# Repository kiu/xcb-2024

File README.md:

# xcb-2024
The cross communication badge (xcb) was created for a two day internal company conference. Its main purpose was to gamify communication and networking across the 150 participants.

<sup>Additional images can be found in the [img](img/) directory</sup>

# Features
The badge features three modes: Conference, Play and Sensor.

In <ins>conference mode</ins> each badge transmits its unique ID every 30 seconds. Any badge receiving two transmissions from the same badge within 100 seconds will count this as a unique contact. Due to limited infrared power, close proximity between sender and receiver is assumed. The amount of unique contacts is displayed on the LCD screen to gamify in-person encounters.

In addition secret badges are hidden at the event location, offering a treasure hunt for those who want to explore beyond the main conference tracks. The needed hints are printed on [flyers](xcb-2024-flyer.pdf) handed out with the badge. The discovery of these secret badges is encoded in the display as single segments to easily compare progress between participants.

It was important to me that the badge could be re-used after the conference so I added two additional modes.

In <ins>play mode</ins> the badge features a version of the popular game Simon https://en.wikipedia.org/wiki/Simon_(game) (in Germany known as Senso https://de.wikipedia.org/wiki/Senso_(Spiel)). People can chase a high score, which can also be displayed when in conference mode.

In <ins>sensor mode</ins> the badge transforms into a temperature and humidity display with min/max functionality. Powered by USB the badge can continue to operate in the home or office.

On the back of this stacked PCB assembly (preventing any electrical shorts while wearing) the participants can find a [silk screened word puzzle](img/xcb-2024-bottom-revb-render-back.png) containing the names of the employees of the company.

## Video
There is a short video highlighting all badge features on youtube: https://youtu.be/XA52-lHTVL4

# Hardware
The hardware is [straight forward](kicad/xcb-2024-top-revb-schematic.png). Powered by two CR2032 coin cells or USB, a STM32, a three digit LCD display, an infrared receiver/transmitter, a buzzer, four capacitive touch buttons and a temperature and humidity sensor. All neatly packed into a wearable badge.

# Repository
- [datasheets](datasheets/): Datasheets of most components
- [firmware](firmware/): STM32CubeIDE project
- [kicad](kicad/): KiCad schematics, PCBs and BOM for single+panelized badge and flash adapter
- [tools](tools/): Helper scripts to generate buzzer note table, mass flashing with auto ID increment and masked word puzzle generator

# License
This project is licensed under the Creative Commons Attribution-NonCommercial 3.0 Unported (CC BY-NC 3.0) license. Use of the company name and company logo in any form is not covered by this license.

# Thanks <3
Thanks to Fabian for helping out on the flyer design and Andrii, Maria (+Sebastian), Monika, Niels (+Milla) for working hard doing the final mechanical assembly!

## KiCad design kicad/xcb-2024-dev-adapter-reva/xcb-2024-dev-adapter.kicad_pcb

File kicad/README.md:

# kicad

<sup>Additional images can be found in the [img](../img/) directory</sup>

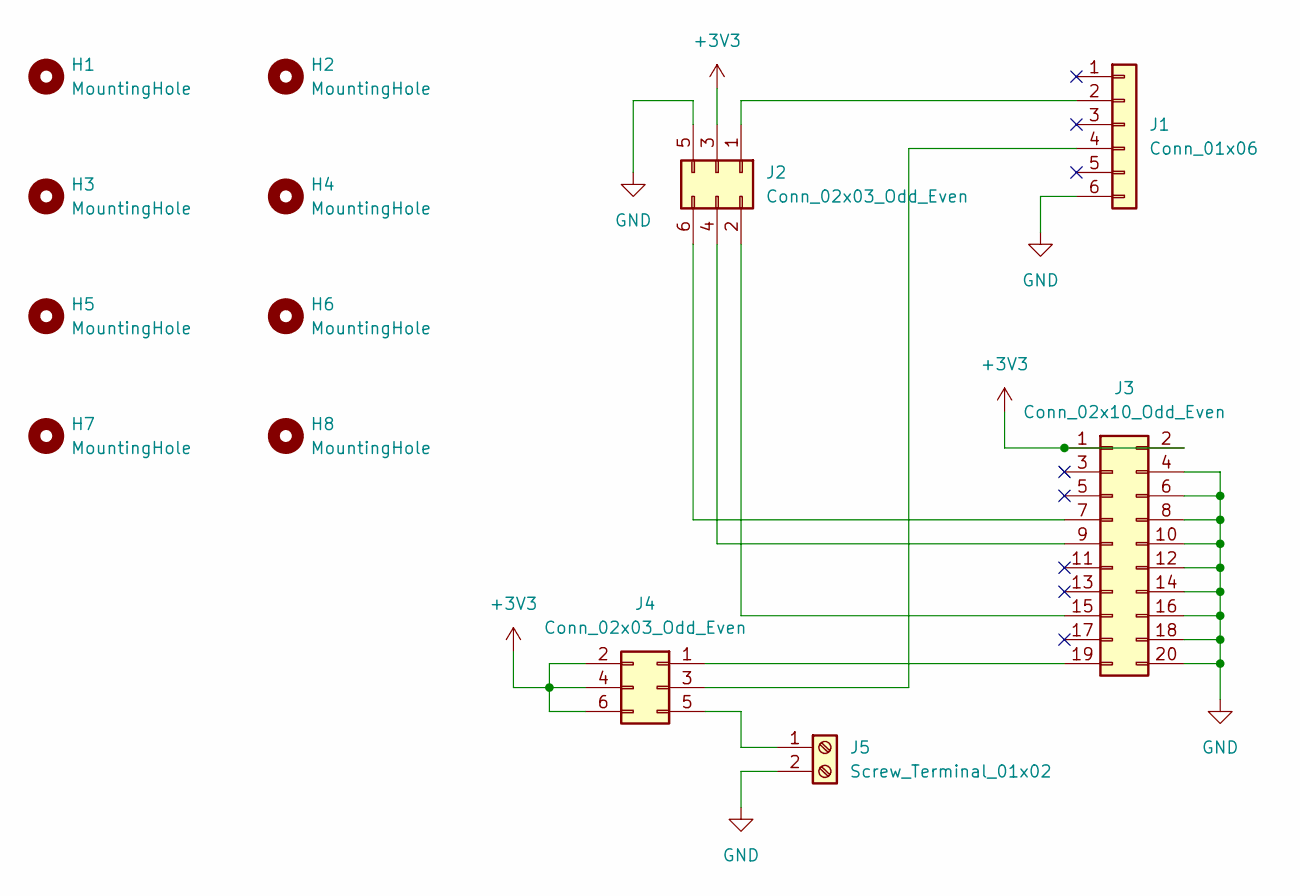
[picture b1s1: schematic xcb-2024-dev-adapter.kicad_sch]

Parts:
H1, H2, H3, H4, H5, H6, H7, H8: MountingHole; MountingHole_3.2mm_M3_DIN965
J1: Conn_01x06; PinSocket_1x06_P2.54mm_Vertical
J2, J4: Conn_02x03_Odd_Even; PinHeader_2x03_P2.54mm_Vertical
J3: Conn_02x10_Odd_Even; IDC-Header_2x10_P2.54mm_Vertical
J5: Screw_Terminal_01x02; TerminalBlock_bornier-2_P5.08mm

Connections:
+3V3: J2.3, J3.1, J3.2, J4.2, J4.4, J4.6
GND: J1.6, J2.5, J3.4, J3.6, J3.8, J3.10, J3.12, J3.14, J3.16, J3.18, J3.20, J5.2
unnamed: J1.2, J2.1
unnamed: J1.4, J4.3
unnamed: J2.2, J3.15
unnamed: J2.4, J3.9
unnamed: J2.6, J3.7
unnamed: J3.19, J4.1
unnamed: J4.5, J5.1

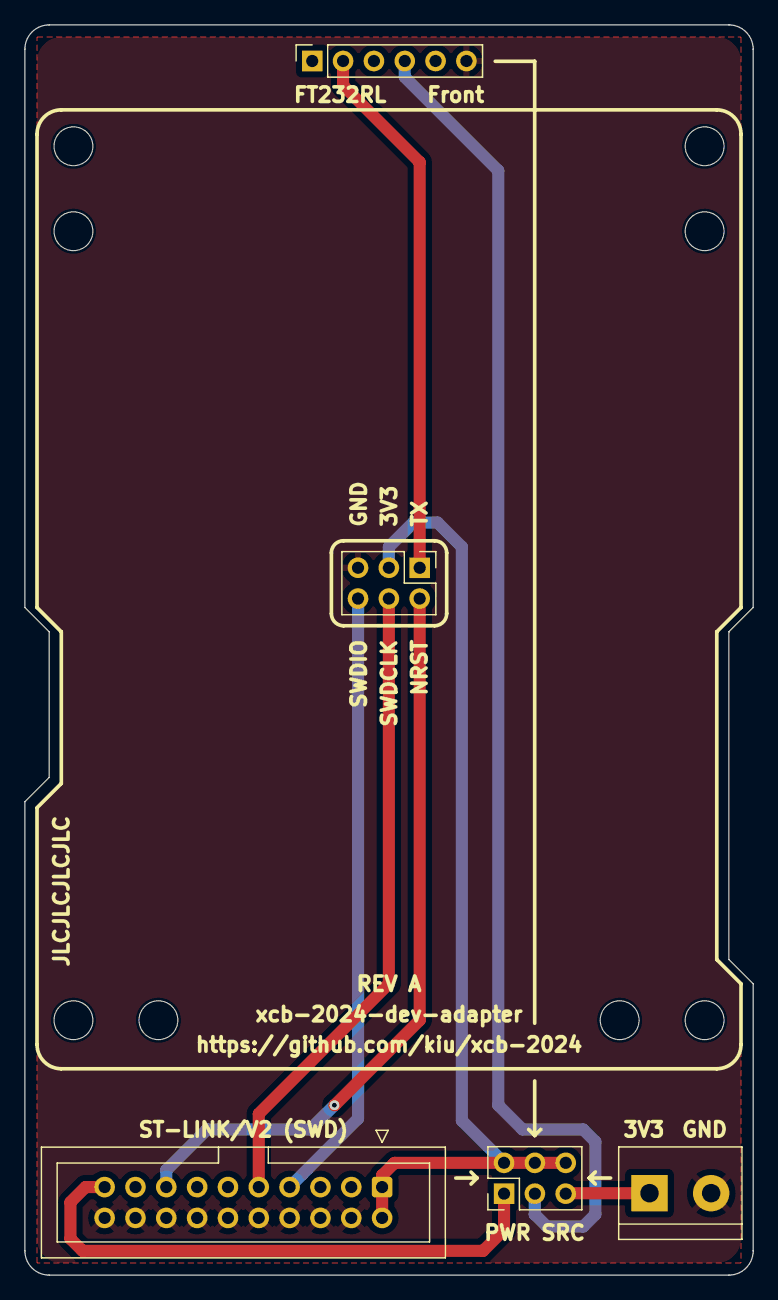
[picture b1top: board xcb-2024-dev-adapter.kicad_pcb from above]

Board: 2 copper layers, 60.0 x 103.0 mm, 13 parts (0 on the bottom side), 9 nets.

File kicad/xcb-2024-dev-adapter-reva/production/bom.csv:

Designator,Footprint,Quantity,Value,LCSC Part #
"H1, H2, H3, H4, H5, H6, H7, H8",MountingHole_3.2mm_M3_DIN965,8,MountingHole,
J1,PinSocket_1x06_P2.54mm_Vertical,1,Conn_01x06,
"J2, J4",PinHeader_2x03_P2.54mm_Vertical,2,Conn_02x03_Odd_Even,
J3,IDC-Header_2x10_P2.54mm_Vertical,1,Conn_02x10_Odd_Even,
J5,TerminalBlock_bornier-2_P5.08mm,1,Screw_Terminal_01x02,

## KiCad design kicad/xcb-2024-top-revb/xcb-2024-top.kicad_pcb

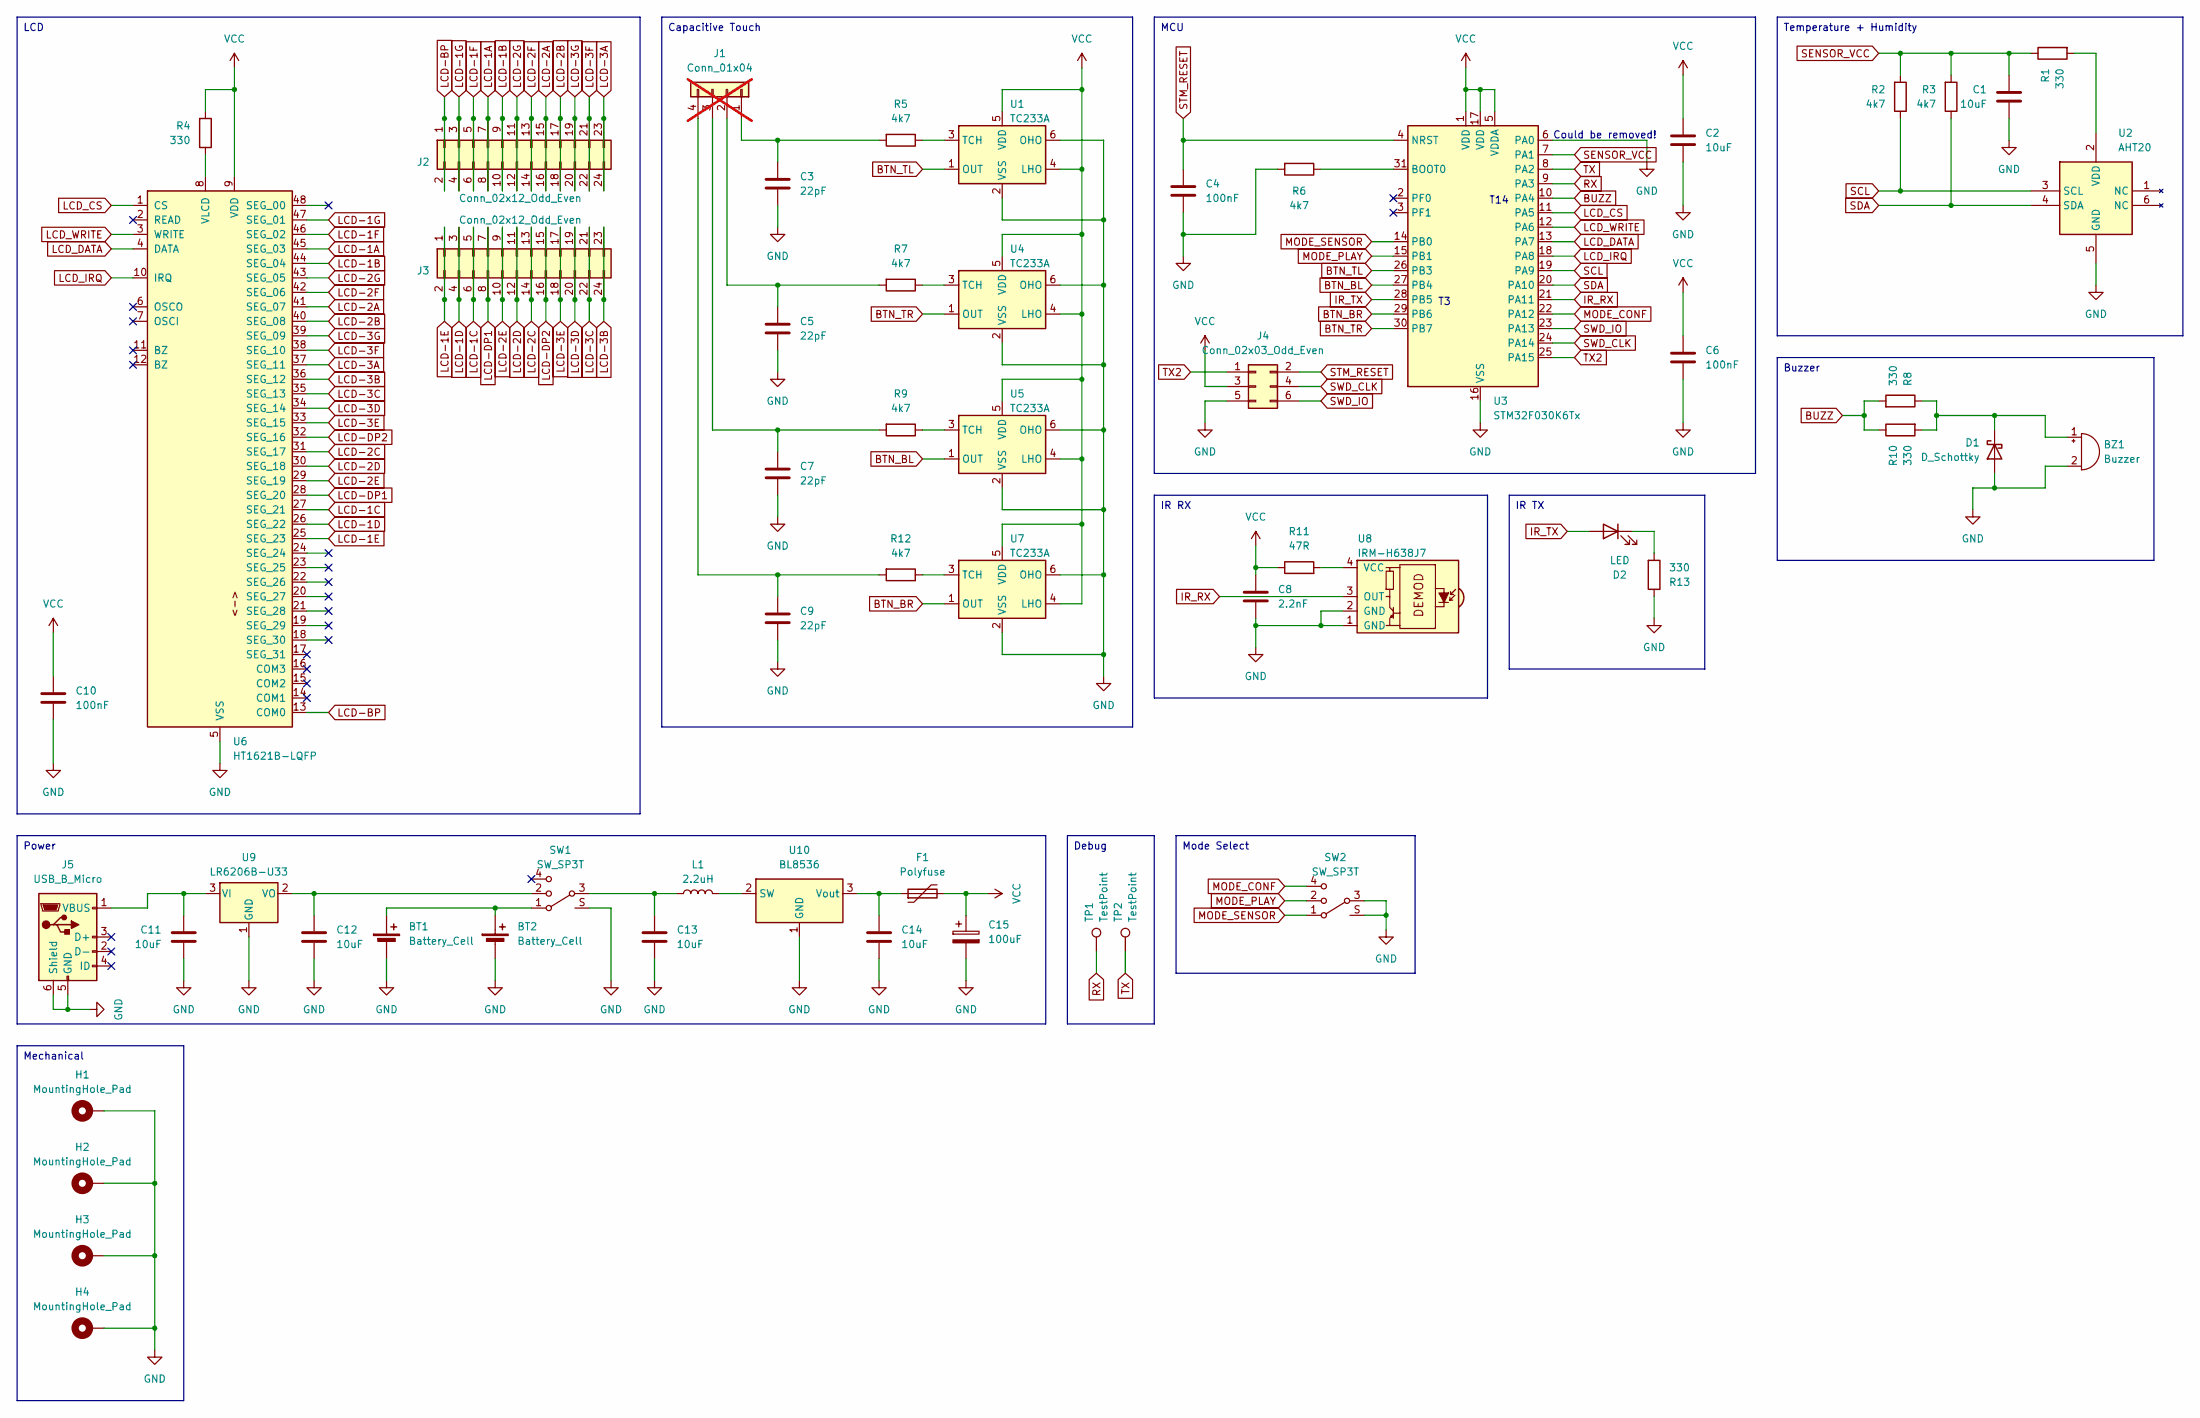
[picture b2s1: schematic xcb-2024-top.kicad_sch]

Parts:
BT1, BT2: Battery_Cell; BatteryHolder_CR2032-BS-6-1; JLC C70377
BZ1: Buzzer; MLT-7525; JLC C95299
C1, C2, C11, C12, C13, C14: 10uF; C_0805_2012Metric; JLC C15850
C3, C5, C7, C9: 22pF; C_0805_2012Metric; JLC C1804
C4, C6, C10: 100nF; C_0805_2012Metric; JLC C49678
C8: 2.2nF; C_0805_2012Metric; JLC C36576
C15: 100uF; CP_EIA-3528-21_Kemet-B_rotated; JLC C16133
D1: D_Schottky; D_SOD-123; JLC C8598
D2: LED; LED_0805_2012Metric; JLC C131250
F1: Polyfuse; Fuse_0805_2012Metric; JLC C2897461
H1, H2, H3, H4: MountingHole_Pad; MountingHole_3.2mm_M3_DIN965_Pad_TopBottom
J1: Conn_01x04; XEMPUS Logo 4 Touch; not fitted
J2, J3: Conn_02x12_Odd_Even; PinSocket_2x12_P2.54mm_Vertical_SMD_rotated; JLC C3975157
J4: Conn_02x03_Odd_Even; PinSocket_2x03_P2.54mm_Vertical_SMD_rotated; JLC C5160818
J5: USB_B_Micro; USB_Micro_MICRO QTZB5.5_C2681557; JLC C2681557
L1: 2.2uH; L_0805_2012Metric; JLC C1043
R1, R4, R8, R10, R13: 330; R_0805_2012Metric; JLC C17630
R2, R3, R5, R6, R7, R9, R12: 4k7; R_0805_2012Metric; JLC C17673
R11: 47R; R_0805_2012Metric; JLC C17714
SW1, SW2: SW_SP3T; SW_SP3T_SSSS812201; JLC C160878
TP1, TP2: TestPoint; TestPoint_Pad_1.0x1.0mm
U1, U4, U5, U7: TC233A; SOT-23-6_rotated; JLC C2798022
U2: AHT20; JLC C2757850
U3: STM32F030K6Tx; LQFP-32_7x7mm_P0.8mm; JLC C46830
U6: HT1621B-LQFP; LQFP-48_7x7mm_P0.5mm; JLC C7532
U8: IRM-H638J7; JLC C414640
U9: LR6206B-U33; SOT-23-3; JLC C5336486
U10: BL8536; SOT-23-3; JLC C97793

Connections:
BTN_BL: U3.27 (PB4), U5.1 (OUT)
BTN_BR: U3.29 (PB6), U7.1 (OUT)
BTN_TL: U1.1 (OUT), U3.26 (PB3)
BTN_TR: U3.30 (PB7), U4.1 (OUT)
BUZZ: R8.2, R10.1, U3.10 (PA4)
GND: BT1.2 (-), BT2.2 (-), BZ1.2 (+), C1.1, C2.1, C3.1, C4.1, C5.1, C6.1, C7.1, C8.1, C9.1, C10.1, C11.1, C12.1, C13.1, C14.1, C15.2, D1.2 (A), H1.1, H2.1, H3.1, H4.1, J4.5, J5.5 (GND), J5.6 (Shield), R6.2, R13.1, SW1.S, SW2.3, SW2.S, U1.2 (VSS), U1.6 (OHO), U2.5 (GND), U3.6 (PA0), U3.16 (VSS), U3.32 (VSS), U4.2 (VSS), U4.6 (OHO), U5.2 (VSS), U5.6 (OHO), U6.5 (VSS), U7.2 (VSS), U7.6 (OHO), U8.1 (GND), U8.2 (GND), U9.1 (GND), U10.1 (GND)
IR_RX: U3.21 (PA11), U8.3 (OUT)
IR_TX: D2.2 (A), U3.28 (PB5)
LCD-1A: J2.7, J2.8, U6.45 (SEG_03)
LCD-1B: J2.9, J2.10, U6.44 (SEG_04)
LCD-1C: J3.5, J3.6, U6.27 (SEG_21)
LCD-1D: J3.3, J3.4, U6.26 (SEG_22)
LCD-1E: J3.1, J3.2, U6.25 (SEG_23)
LCD-1F: J2.5, J2.6, U6.46 (SEG_02)
LCD-1G: J2.3, J2.4, U6.47 (SEG_01)
LCD-2A: J2.15, J2.16, U6.41 (SEG_07)
LCD-2B: J2.17, J2.18, U6.40 (SEG_08)
LCD-2C: J3.13, J3.14, U6.31 (SEG_17)
LCD-2D: J3.11, J3.12, U6.30 (SEG_18)
LCD-2E: J3.9, J3.10, U6.29 (SEG_19)
LCD-2F: J2.13, J2.14, U6.42 (SEG_06)
LCD-2G: J2.11, J2.12, U6.43 (SEG_05)
LCD-3A: J2.23, J2.24, U6.37 (SEG_11)
LCD-3B: J3.23, J3.24, U6.36 (SEG_12)
LCD-3C: J3.21, J3.22, U6.35 (SEG_13)
LCD-3D: J3.19, J3.20, U6.34 (SEG_14)
LCD-3E: J3.17, J3.18, U6.33 (SEG_15)
LCD-3F: J2.21, J2.22, U6.38 (SEG_10)
LCD-3G: J2.19, J2.20, U6.39 (SEG_09)
LCD-BP: J2.1, J2.2, U6.13 (COM0)
LCD-DP1: J3.7, J3.8, U6.28 (SEG_20)
LCD-DP2: J3.15, J3.16, U6.32 (SEG_16)
LCD_CS: U3.11 (PA5), U6.1 (CS)
LCD_DATA: U3.13 (PA7), U6.4 (DATA)
LCD_IRQ: U3.18 (PA8), U6.10 (IRQ)
LCD_WRITE: U3.12 (PA6), U6.3 (WRITE)
MODE_CONF: SW2.4, U3.22 (PA12)
MODE_PLAY: SW2.2, U3.15 (PB1)
MODE_SENSOR: SW2.1, U3.14 (PB0)
unnamed: BT1.1 (+), BT2.1 (+), SW1.1
unnamed: BZ1.1 (-), D1.1 (K), R8.1, R10.2
unnamed: C13.2, L1.1, SW1.3
unnamed: D2.1 (K), R13.2
unnamed: C3.2, J1.1, R5.2
unnamed: C5.2, J1.2, R7.2
unnamed: C7.2, J1.3, R9.2
unnamed: C9.2, J1.4, R12.2
unnamed: C11.2, J5.1 (VBUS), U9.3 (VI)
unnamed: R5.1, U1.3 (TCH)
unnamed: R1.2, U2.2 (VDD)
unnamed: R6.1, U3.31 (BOOT0)
unnamed: R7.1, U4.3 (TCH)
unnamed: R9.1, U5.3 (TCH)
unnamed: R4.1, U6.8 (VLCD)
unnamed: R12.1, U7.3 (TCH)
unnamed: R11.2, U8.4 (VCC)
unnamed: C12.2, SW1.2, U9.2 (VO)
unnamed: L1.2, U10.2 (SW)
unnamed: C14.2, F1.1, U10.3 (Vout)
RX: TP1.1, U3.9 (PA3)
SCL: R2.1, U2.3 (SCL), U3.19 (PA9)
SDA: R3.1, U2.4 (SDA), U3.20 (PA10)
SENSOR_VCC: C1.2, R1.1, R2.2, R3.2, U3.7 (PA1)
STM_RESET: C4.2, J4.2, U3.4 (NRST)
SWD_CLK: J4.4, U3.24 (PA14)
SWD_IO: J4.6, U3.23 (PA13)
TX: TP2.1, U3.8 (PA2)
TX2: J4.1, U3.25 (PA15)
VCC: C2.2, C6.2, C8.2, C10.2, C15.1, F1.2, J4.3, R4.2, R11.1, U1.4 (LHO), U1.5 (VDD), U3.1 (VDD), U3.5 (VDDA), U3.17 (VDD), U4.4 (LHO), U4.5 (VDD), U5.4 (LHO), U5.5 (VDD), U6.9 (VDD), U7.4 (LHO), U7.5 (VDD)

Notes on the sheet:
MCU
Mechanical
Power
Mode Select
IR RX
LCD
IR TX
Temperature + Humidity
Buzzer
Capacitive Touch
Debug
Could be removed!
T14

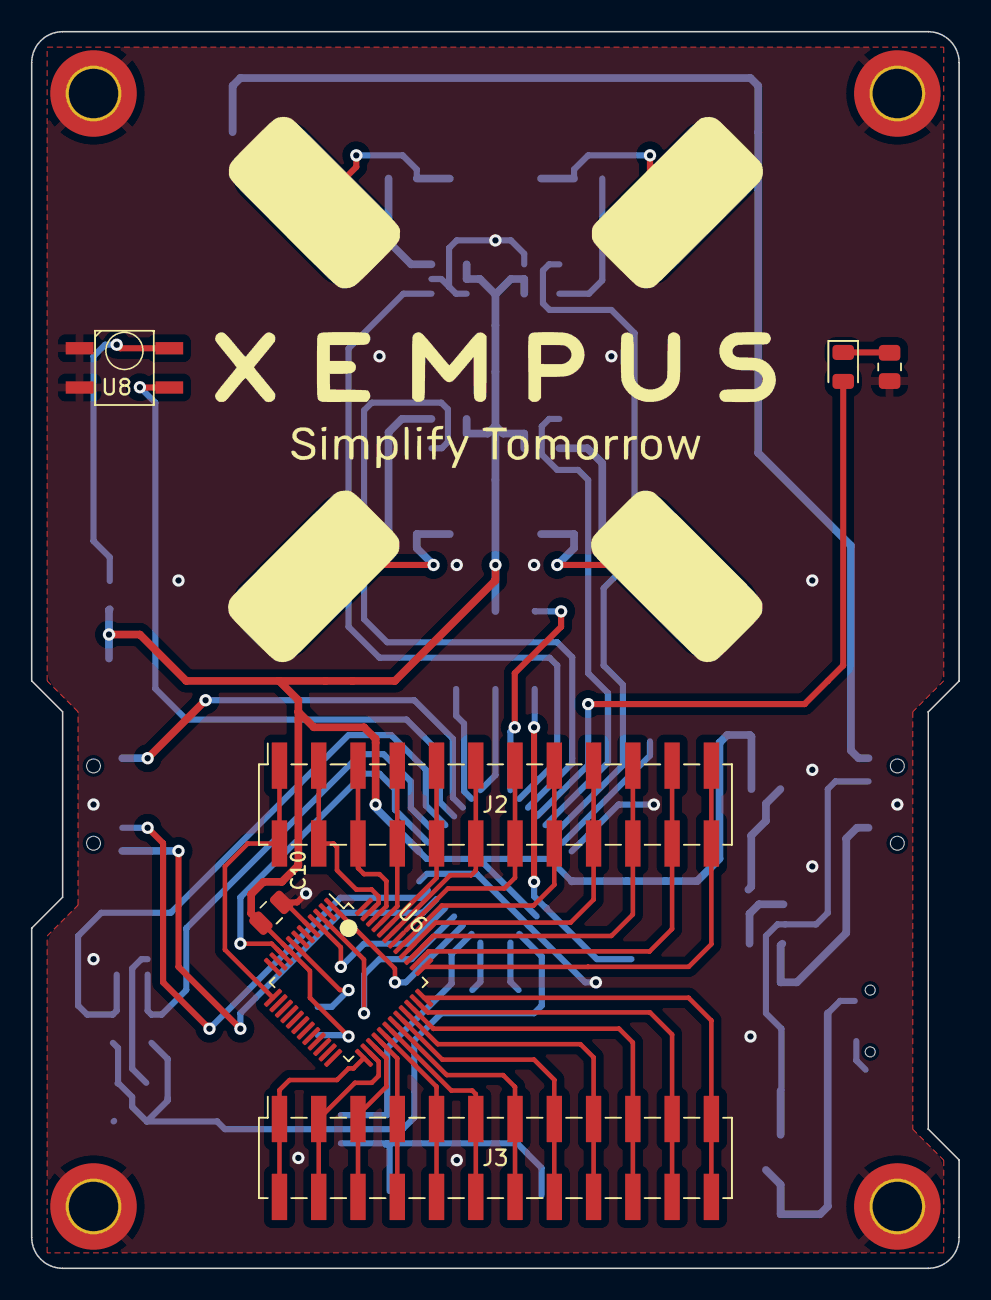
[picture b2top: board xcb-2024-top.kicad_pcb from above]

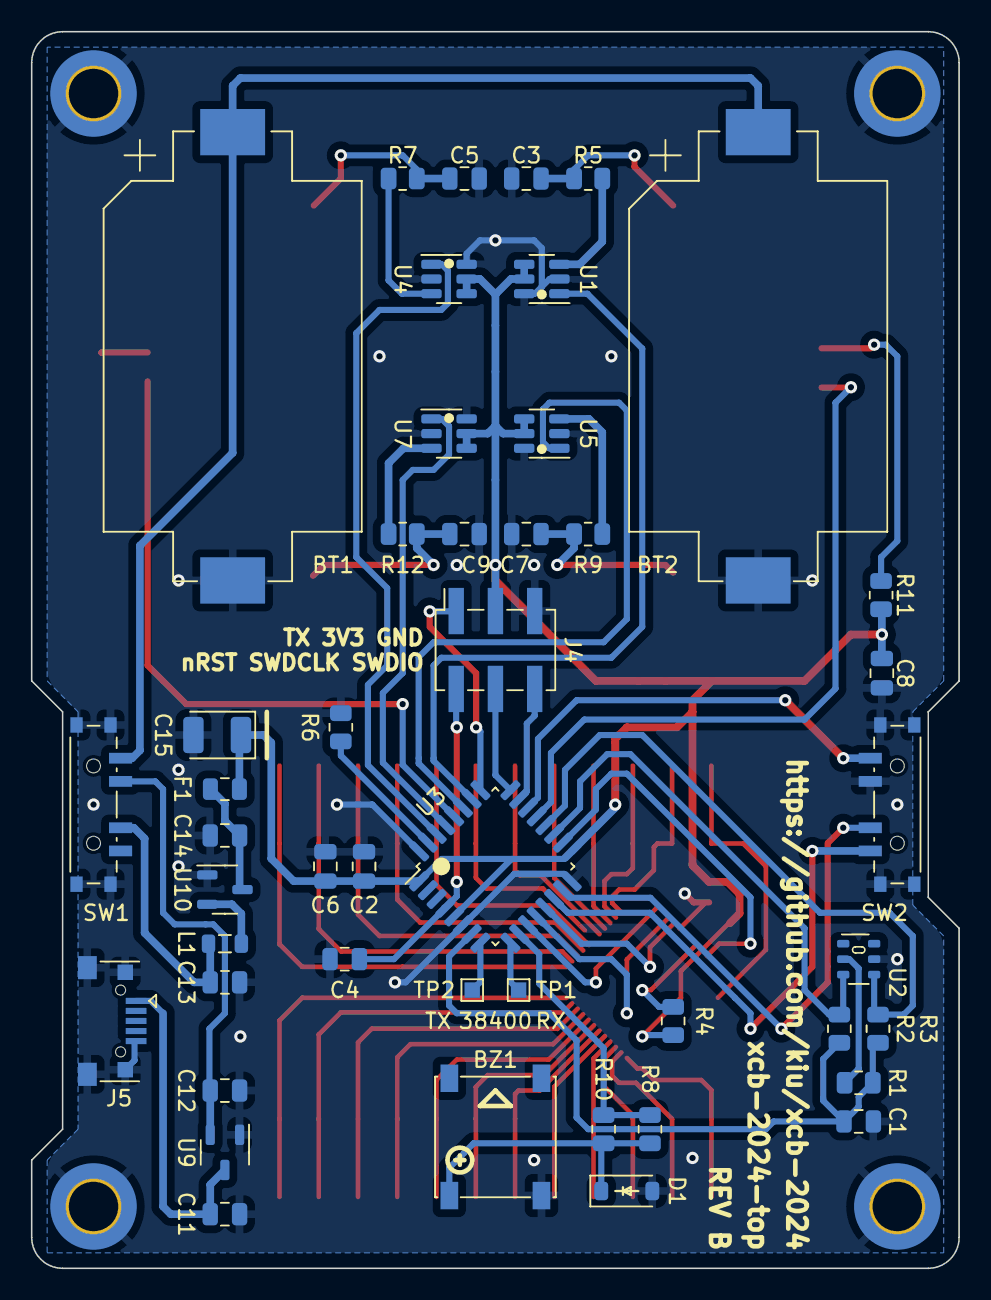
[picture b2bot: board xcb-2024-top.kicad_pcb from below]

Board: 2 copper layers, 60.0 x 80.0 mm, 58 parts (46 on the bottom side), 69 nets.

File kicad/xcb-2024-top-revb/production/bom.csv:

Designator,Footprint,Quantity,Value,LCSC Part #
"BT1, BT2",BatteryHolder_CR2032-BS-6-1,2,Battery_Cell,C70377
BZ1,MLT-7525,1,Buzzer,C95299
"C1, C11, C12, C13, C14, C2",0805,6,10uF,C15850
"C10, C4, C6",0805,3,100nF,C49678
C15,CP_EIA-3528-21_Kemet-B_rotated,1,100uF,C16133
"C3, C5, C7, C9",0805,4,22pF,C1804
C8,0805,1,2.2nF,C36576
D1,D_SOD-123,1,D_Schottky,C8598
D2,0805,1,LED,C131250
F1,0805,1,Polyfuse,C2897461
"J2, J3",PinSocket_2x12_P2.54mm_Vertical_SMD_rotated,2,Conn_02x12_Odd_Even,C3975157
J4,PinSocket_2x03_P2.54mm_Vertical_SMD_rotated,1,Conn_02x03_Odd_Even,C5160818
J5,USB_Micro_MICRO QTZB5.5_C2681557,1,USB_B_Micro,C2681557
L1,0805,1,2.2uH,C1043
"R1, R10, R13, R4, R8",0805,5,330,C17630
R11,0805,1,47R,C17714
"R12, R2, R3, R5, R6, R7, R9",0805,7,4k7,C17673
"SW1, SW2",SW_SP3T_SSSS812201,2,SW_SP3T,C160878
"U1, U4, U5, U7",SOT-23-6_rotated,4,TC233A,C2798022
U10,SOT-23-3,1,BL8536,
U2,AHT20,1,AHT20,C2757850
U3,LQFP-32_7x7mm_P0.8mm,1,STM32F030K6Tx,C46830
U6,LQFP-48_7x7mm_P0.5mm,1,HT1621B-LQFP,C7532
U8,IRM-H638J7,1,IRM-H638J7,C414640
U9,SOT-23-3,1,LR6206B-U33,C5336486

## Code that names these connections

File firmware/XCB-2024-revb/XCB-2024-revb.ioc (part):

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Mcu.Name=STM32F030K6Tx
Mcu.Package=LQFP32
Mcu.UserName=STM32F030K6Tx
PA1.GPIOParameters=GPIO_Label
PA1.GPIO_Label=SENSOR_VCC
PA1.Signal=GPIO_Output
PA10.Mode=I2C
PA10.Signal=I2C1_SDA
PA11.GPIOParameters=GPIO_PuPd,GPIO_Label,GPIO_ModeDefaultEXTI
PA11.GPIO_Label=IR_RX
PA11.GPIO_ModeDefaultEXTI=GPIO_MODE_IT_RISING
PA11.GPIO_PuPd=GPIO_NOPULL
PA11.Signal=GPXTI11
PA12.GPIOParameters=GPIO_PuPd,GPIO_Label,GPIO_ModeDefaultEXTI
PA12.GPIO_Label=MODE_CONF
PA12.GPIO_ModeDefaultEXTI=GPIO_MODE_IT_FALLING
PA12.GPIO_PuPd=GPIO_PULLUP
PA12.Signal=GPXTI12
PA13.Mode=Serial_Wire
PA13.Signal=SYS_SWDIO
PA14.Mode=Serial_Wire
PA14.Signal=SYS_SWCLK
PA15.Mode=Asynchronous
PA15.Signal=USART1_RX
PA2.Mode=Asynchronous
PA2.Signal=USART1_TX
PA4.GPIOParameters=GPIO_Label
PA4.GPIO_Label=BUZZ
PA4.Signal=S_TIM14_CH1
PA5.GPIOParameters=GPIO_Label
PA5.GPIO_Label=LCD_CS
PA5.Signal=GPIO_Output
PA6.GPIOParameters=GPIO_Label
PA6.GPIO_Label=LCD_WRITE
PA6.Signal=GPIO_Output
PA7.GPIOParameters=GPIO_Label
PA7.GPIO_Label=LCD_DATA
PA7.Signal=GPIO_Output
PA8.GPIOParameters=GPIO_PuPd,GPIO_Label,GPIO_ModeDefaultEXTI
PA8.GPIO_Label=LCD_IRQ
PA8.GPIO_ModeDefaultEXTI=GPIO_MODE_IT_FALLING
PA8.GPIO_PuPd=GPIO_PULLUP
PA8.Signal=GPXTI8
PA9.Mode=I2C
PA9.Signal=I2C1_SCL
PB0.GPIOParameters=GPIO_PuPd,GPIO_Label,GPIO_ModeDefaultEXTI
PB0.GPIO_Label=MODE_SENSOR
PB0.GPIO_ModeDefaultEXTI=GPIO_MODE_IT_FALLING
PB0.GPIO_PuPd=GPIO_PULLUP
PB0.Signal=GPXTI0
PB1.GPIOParameters=GPIO_PuPd,GPIO_Label,GPIO_ModeDefaultEXTI
PB1.GPIO_Label=MODE_PLAY
PB1.GPIO_ModeDefaultEXTI=GPIO_MODE_IT_FALLING
PB1.GPIO_PuPd=GPIO_PULLUP
PB1.Signal=GPXTI1
PB3.GPIOParameters=GPIO_PuPd,GPIO_Label,GPIO_ModeDefaultEXTI
PB3.GPIO_Label=BTN_TL
PB3.GPIO_ModeDefaultEXTI=GPIO_MODE_IT_FALLING
PB3.GPIO_PuPd=GPIO_PULLUP
PB3.Signal=GPXTI3
PB4.GPIOParameters=GPIO_PuPd,GPIO_Label,GPIO_ModeDefaultEXTI
PB4.GPIO_Label=BTN_BL
PB4.GPIO_ModeDefaultEXTI=GPIO_MODE_IT_FALLING
PB4.GPIO_PuPd=GPIO_PULLUP
PB4.Signal=GPXTI4
PB5.GPIOParameters=GPIO_Label
PB5.GPIO_Label=IR_TX
PB5.Signal=S_TIM3_CH2
PB6.GPIOParameters=GPIO_PuPd,GPIO_Label,GPIO_ModeDefaultEXTI
PB6.GPIO_Label=BTN_BR
PB6.GPIO_ModeDefaultEXTI=GPIO_MODE_IT_FALLING
PB6.GPIO_PuPd=GPIO_PULLUP
PB6.Signal=GPXTI6
PB7.GPIOParameters=GPIO_PuPd,GPIO_Label,GPIO_ModeDefaultEXTI
PB7.GPIO_Label=BTN_TR
PB7.GPIO_ModeDefaultEXTI=GPIO_MODE_IT_FALLING
PB7.GPIO_PuPd=GPIO_PULLUP
PB7.Signal=GPXTI7
board=custom

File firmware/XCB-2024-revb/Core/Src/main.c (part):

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
	uint8_t next = 0xFF;
	uint8_t match = 0;
	if (!HAL_GPIO_ReadPin(MODE_CONF_GPIO_Port, MODE_CONF_Pin)) {
		next = MODE_CONF;
		match++;
	}

	if (!HAL_GPIO_ReadPin(MODE_PLAY_GPIO_Port, MODE_PLAY_Pin)) {
		next = MODE_PLAY;
		match++;
	}
	if (!HAL_GPIO_ReadPin(MODE_SENSOR_GPIO_Port, MODE_SENSOR_Pin)) {
		next = MODE_SENSOR;
		match++;
	}
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}

void buttonClear() {
	irq_state &= ~BTN_TL_Pin;
	irq_state &= ~BTN_TR_Pin;
	irq_state &= ~BTN_BR_Pin;
	irq_state &= ~BTN_BL_Pin;
}

void buttonCheck() {
	uint8_t btn = 0;

	if (irq_state & BTN_TL_Pin) {
		irq_state &= ~BTN_TL_Pin;
		btn |= (1 << 0);
	}
	if (irq_state & BTN_TR_Pin) {
		irq_state &= ~BTN_TR_Pin;
		btn |= (1 << 1);
	}
	if (irq_state & BTN_BR_Pin) {
		irq_state &= ~BTN_BR_Pin;
		btn |= (1 << 2);
	}
	if (irq_state & BTN_BL_Pin) {
		irq_state &= ~BTN_BL_Pin;
		btn |= (1 << 3);
	}

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void HAL_GPIO_EXTI_Callback(uint16_t pin) {
	irq_state |= pin;

	if ((pin & MODE_CONF_Pin) | (pin & MODE_PLAY_Pin) | (pin & MODE_SENSOR_Pin)) {
		mode_switch = true;
	}

	if (pin & LCD_IRQ_Pin) {
		tick = true;
	}

	if (pin & IR_RX_Pin) {
		if (mode == MODE_CONF) {
			confIRRX_gpio_dec();
		}
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	__HAL_RCC_GPIOB_CLK_ENABLE();

	/*Configure GPIO pin Output Level */
	HAL_GPIO_WritePin(GPIOA, SENSOR_VCC_Pin | LCD_CS_Pin | LCD_WRITE_Pin | LCD_DATA_Pin, GPIO_PIN_RESET);

	/*Configure GPIO pins : PF0 PF1 */
	GPIO_InitStruct.Pin = GPIO_PIN_0 | GPIO_PIN_1;
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	GPIO_InitStruct.Pull = GPIO_NOPULL;
	HAL_GPIO_Init(GPIOF, &GPIO_InitStruct);

	/*Configure GPIO pins : PA0 PA3 */
	GPIO_InitStruct.Pin = GPIO_PIN_0 | GPIO_PIN_3;
	GPIO_InitStruct.Mode = GPIO_MODE_ANALOG;
	GPIO_InitStruct.Pull = GPIO_NOPULL;
	HAL_GPIO_Init(GPIOA, &GPIO_InitStruct);

	/*Configure GPIO pins : SENSOR_VCC_Pin LCD_CS_Pin LCD_WRITE_Pin LCD_DATA_Pin */
	GPIO_InitStruct.Pin = SENSOR_VCC_Pin | LCD_CS_Pin | LCD_WRITE_Pin | LCD_DATA_Pin;
	GPIO_InitStruct.Mode = GPIO_MODE_OUTPUT_PP;
	GPIO_InitStruct.Pull = GPIO_NOPULL;
	GPIO_InitStruct.Speed = GPIO_SPEED_FREQ_LOW;
	HAL_GPIO_Init(GPIOA, &GPIO_InitStruct);

	/*Configure GPIO pins : MODE_SENSOR_Pin MODE_PLAY_Pin BTN_TL_Pin BTN_BL_Pin
	 BTN_BR_Pin BTN_TR_Pin */
	GPIO_InitStruct.Pin = MODE_SENSOR_Pin | MODE_PLAY_Pin | BTN_TL_Pin | BTN_BL_Pin | BTN_BR_Pin | BTN_TR_Pin;
	GPIO_InitStruct.Mode = GPIO_MODE_IT_FALLING;
	GPIO_InitStruct.Pull = GPIO_PULLUP;
	HAL_GPIO_Init(GPIOB, &GPIO_InitStruct);

	/*Configure GPIO pins : LCD_IRQ_Pin MODE_CONF_Pin */
	GPIO_InitStruct.Pin = LCD_IRQ_Pin | MODE_CONF_Pin;
	GPIO_InitStruct.Mode = GPIO_MODE_IT_FALLING;
	GPIO_InitStruct.Pull = GPIO_PULLUP;
	HAL_GPIO_Init(GPIOA, &GPIO_InitStruct);

	/*Configure GPIO pin : IR_RX_Pin */
	GPIO_InitStruct.Pin = IR_RX_Pin;
	GPIO_InitStruct.Mode = GPIO_MODE_IT_RISING;
	GPIO_InitStruct.Pull = GPIO_NOPULL;
	HAL_GPIO_Init(IR_RX_GPIO_Port, &GPIO_InitStruct);

	/* EXTI interrupt init*/
	HAL_NVIC_SetPriority(EXTI0_1_IRQn, 0, 0);
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

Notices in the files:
firmware/XCB-2024-revb/Core/Src/main.c:
Copyright (c) 2024 STMicroelectronics.
All rights reserved.
This software is licensed under terms that can be found in the LICENSE file
